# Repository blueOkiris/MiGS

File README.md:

# MiGS (Microcontroller Game System)

## Description

A cheap and easy to program game console based on multiple microcontrollers interacting.

## Building

- Dependencies:
  + Linux System
  + gcc
  + make
  + cmake
  + git
  + gcc-arm-none-eabi
  + libnewlib-arm-none-eabi

To flash the programmer run `make upload-pgrmr PORT=<insert port>`

To build the menu program run `make MigsMenu.ino.hex`

To build the gpu program run `make MigsGpu.uf2`

To flash the ErrorReceiver program, use the Arduino IDE

## System Design

3 Parts: Programming MCU, Logic MCU, and Graphics MCU

__Graphics MCU:__
- Raspberry Pi PICO
- Outputs [sprite-based system to VGA](https://www.youtube.com/watch?v=RmPWcsvGSyk) (which gets [adapted to HDMI](https://www.amazon.com/Monitor-Connector-VENTION-Adapter-Computer/dp/B08GZ159FJ/ref=sr_1_6?crid=1TODLD3WMDJ1C&keywords=vga+to+hdmi&qid=1645044383&sprefix=vga+to+hdm%2Caps%2C127&sr=8-6))
- Learns what to draw via communication with Logic MCU

__Logic MCU:__
- Actually what people program for
- Sends graphics info to Graphics MCU to be drawn since it's underpowered
- Main logic for games
- ATMega328p (i.e. essentially and Arduino UNO)
- Processes controller inputs

__Programming MCU:__
- [Programs the Logic MCU from SD card](https://baldwisdom.com/bootdrive/)
- Provides access to sd card data for the Logic MCU
- Processes controller inputs to actually select a game (menu program "fake")

__Error Receiver__
- Serial connection to programmer for debugging
- Requires enabling debug flag in programmer's .hpp files and connecting programmer 5, 4 to this device's 4, 5

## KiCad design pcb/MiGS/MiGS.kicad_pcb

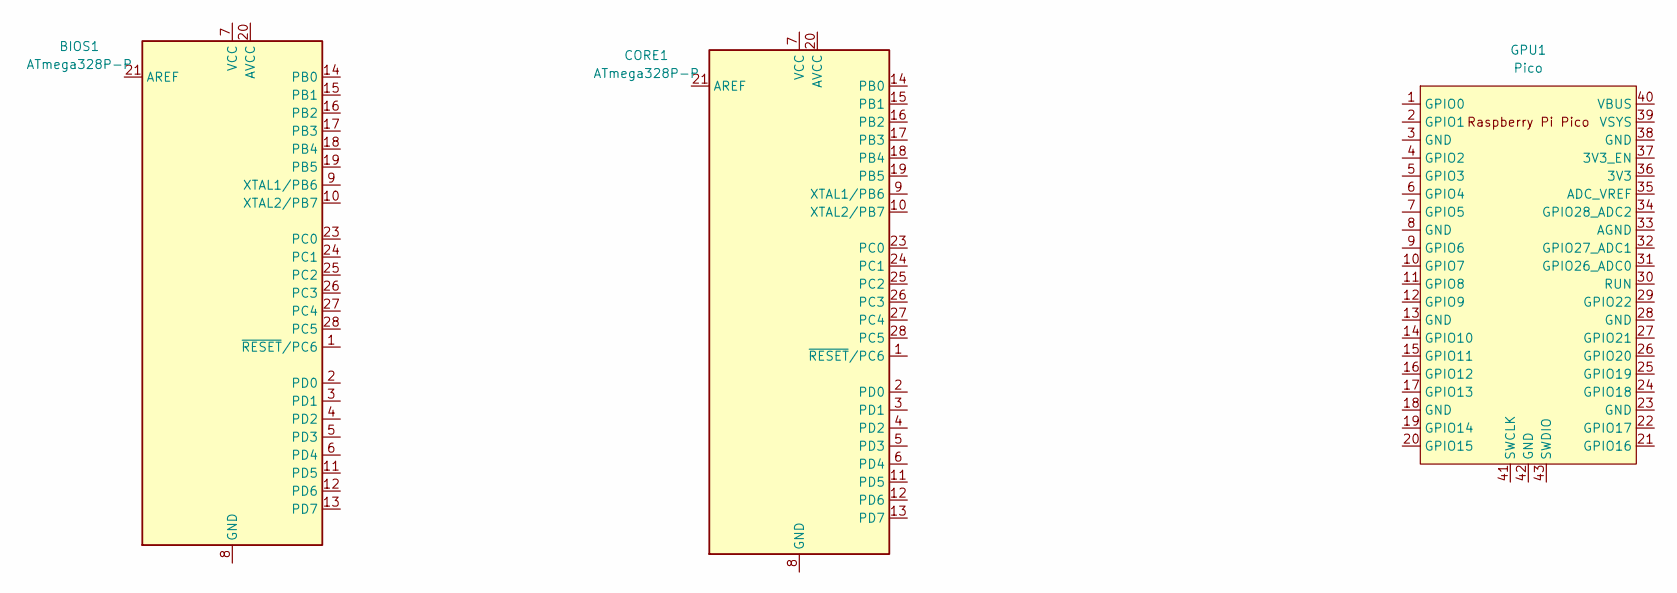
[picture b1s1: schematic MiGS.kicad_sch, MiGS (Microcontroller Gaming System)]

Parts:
BIOS1: ATmega328P-P; DIP-28_W7.62mm
CORE1: ATmega328P-P; DIP-28_W7.62mm
GPU1: Pico; RPi_Pico_SMD_TH

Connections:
unnamed: BIOS1.8 (GND), BIOS1.22 (GND)
unnamed: CORE1.8 (GND), CORE1.22 (GND)

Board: 2 copper layers, 3 parts (0 on the bottom side), 2 nets, no tracks yet.

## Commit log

2022-02-24 Added project setup and AvrProgrammer library to git
2022-02-24 Added note about error receiver program
2022-02-24 Added build system for gpu project
2022-02-25 Got libdvi linking with the PICO example
2022-02-25 Fixed dependency list
2022-03-09 Started on PCB and got DVI working on pico
2022-03-09 Got the Pico (gpu) communicating with main arduino (cpu)
2022-03-09 Decoupled SD card code from AvrProgrammer class
2022-03-09 Started working on the programmer doing resource providing to CPU arduino when not programming
2022-03-09 Added another option to the provide case structure
2022-03-09 Implemented interface for getting data from files
2022-03-09 Implemented communication from Menu to Gpu for text
2022-03-09 Switched to drawing text on tmds buffer in GPU. Demo may work rn
2022-03-10 Switched to sprite system
2022-03-10 Got data from arduino to modify graphics info on gpu
2022-03-10 Started sending sprite info to pico (not working)
